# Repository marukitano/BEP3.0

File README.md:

# BEP3.0

**BEP3.0** is an electronics interface for classic BMW K-series motorcycles.

It was developed to make replacing the original instrument cluster ("Brotbox")
with an aftermarket speedometer easier while keeping the original wiring loom
as intact and reversible as possible.

This repository contains the **production and manufacturing files** for the
BEP3.0.

> **License notice:** The files in this repository may be copied, modified and
> used to build a BEP3.0 for **private, non-commercial purposes**.
> **Commercial use is prohibited.**
>
> The commercial right to sell BEP3.0 units is reserved exclusively to
> **Marcus Knop**. Third-party commercial manufacturing or sales require his
> explicit written permission.

## Supported motorcycles

The BEP3.0 was designed for the classic BMW K-series, including:

- BMW K75
- BMW K100
- BMW K1
- BMW K1100

Compatibility with a particular aftermarket instrument depends on the signals
and inputs supported by that instrument.

## What is in this repository?

The repository contains the files used to produce the BEP3.0 hardware, including
PCB/manufacturing data and related production files.

The files are published so that the project can be studied, preserved, repaired
and rebuilt by private users.

## License

### Allowed

- ✅ View and study the files
- ✅ Copy the files for private, non-commercial use
- ✅ Modify the files for private, non-commercial use
- ✅ Build your own BEP3.0 for private, non-commercial use
- ✅ Have a board manufactured for your own private, non-commercial use
- ✅ Share the files non-commercially if the license and attribution remain

### Not allowed

- ❌ Sell BEP3.0 units
- ❌ Sell bare PCBs based on the BEP3.0 design
- ❌ Sell kits based on the BEP3.0 design
- ❌ Offer paid manufacturing or assembly based on these files
- ❌ Use the BEP3.0 design, or substantial parts of it, in another commercial product
- ❌ Use the files for crowdfunding, pre-orders or other commercial fundraising

**All commercial rights remain reserved by Marcus Knop.**

Only Marcus Knop may offer BEP3.0 products for commercial sale. Commercial
manufacturing by third parties is only permitted with his explicit written
permission.

See [LICENSE](LICENSE) for the complete license terms.

> Because commercial use is restricted, this project is **source-available for
> private/non-commercial use** rather than open source in the OSI/open-hardware
> sense.

## Project page

More information about the BEP3.0:

https://maru-labs.com/portfolio/bep3-0-5/

## Contributions and issues

If you discover an error in the production files or documentation, please open
an issue before manufacturing a board.

## Disclaimer

The files are provided **as-is**, without warranty.

If you manufacture hardware from these files, you are responsible for checking
the design, component choices, manufacturing data, electrical safety and
suitability for your intended use.

---

**BEP3.0 / Maru Labs**  
Copyright © Marcus Knop

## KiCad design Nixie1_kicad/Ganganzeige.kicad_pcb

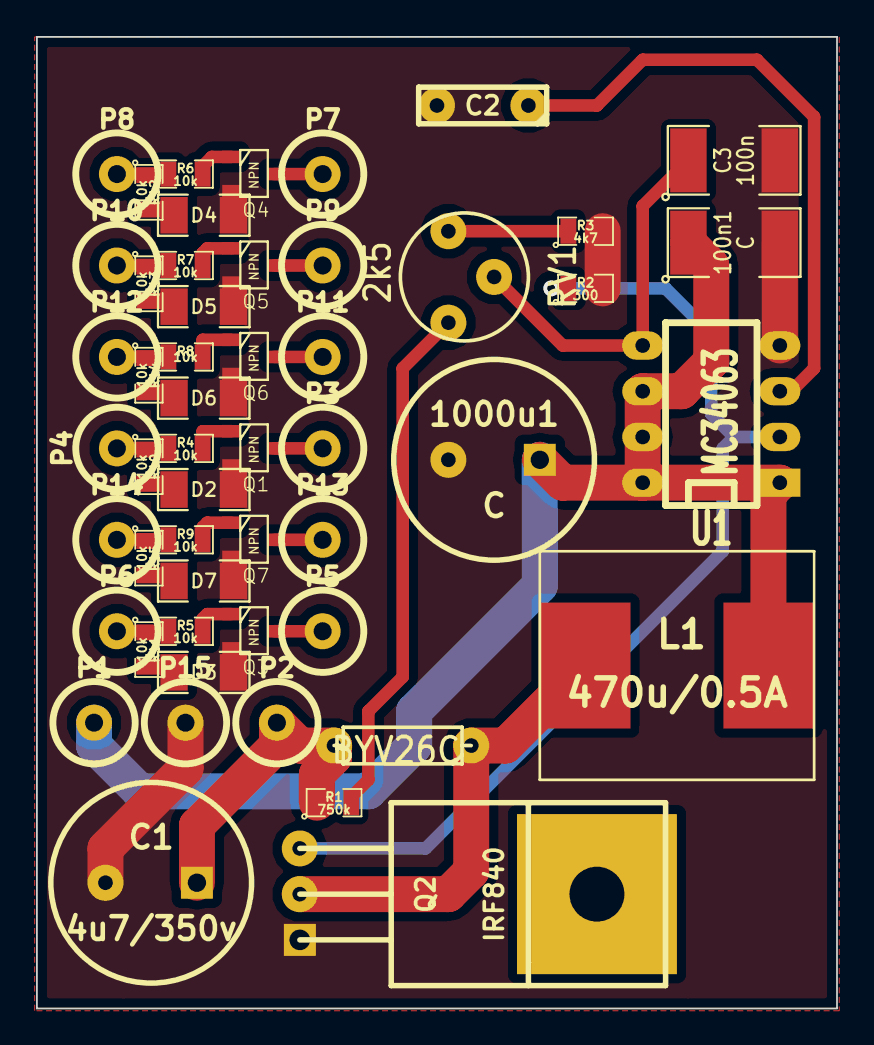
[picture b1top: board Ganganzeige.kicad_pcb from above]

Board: 2 copper layers, 44.4 x 54.0 mm, 52 parts (0 on the bottom side), 33 nets.

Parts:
100n1: C; SM1812L
1000u1: C; C2V10
C1: 4u7/350v; C2V10
C2: 1n; C2
C3: 100n; SM1812L
D1: BYV26C; R3
D2, D3, D4, D5, D6, D7: BYV26C; SM1206
L1: 470u/0.5A; BUZZER
P1, P2, P3, P4, P5, P6, P7, P8, P9, P10, P11, P12, P13, P14, P15: CONN_1; 1pin
Q1, Q3, Q4, Q5, Q6, Q7: NPN; SOT23_INV
Q2: IRF840; TO220
R1: 750k; SM0805
R2: 300; SM0805
R3: 4k7; SM0805
R4, R5, R6, R7, R8, R9, R10, R11, R12, R13, R14, R15: 10k; SM0805
RV1: 2k5; RV2
U1: MC34063; DIP-8__300_ELL

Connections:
GND: 100n1.2, 1000u1.2, C1.2, C2.2, C3.2, D2.2, D3.2, D4.2, D5.2, D6.2, D7.2, P15.1, Q1.1, Q2.1, Q3.1, Q4.1, Q5.1, Q6.1, Q7.1, R2.2, R3.2, U1.4
unnamed: R1.2, RV1.3
unnamed: D1.1, L1.1, Q2.3
unnamed: Q2.2, R2.1, U1.2
unnamed: R3.1, RV1.1
unnamed: C2.1, U1.3
unnamed: C3.1, RV1.2, U1.5
unnamed: D6.1, R14.2
unnamed: D4.1, R12.2
unnamed: P10.1, R7.1, R13.1
unnamed: D5.1, R13.2
unnamed: P12.1, R8.1, R14.1
unnamed: P14.1, R9.1, R15.1
unnamed: D7.1, R15.2
unnamed: D2.1, R10.2
unnamed: D3.1, R11.2
unnamed: P8.1, R6.1, R12.1
unnamed: Q1.2, R4.2
unnamed: P6.1, R5.1, R11.1
unnamed: Q3.2, R5.2
unnamed: Q4.2, R6.2
unnamed: Q5.2, R7.2
unnamed: Q6.2, R8.2
unnamed: Q7.2, R9.2
unnamed: P13.1, Q7.3
unnamed: P4.1, R4.1, R10.1
unnamed: P3.1, Q1.3
unnamed: P5.1, Q3.3
unnamed: P7.1, Q4.3
unnamed: P9.1, Q5.3
unnamed: P11.1, Q6.3
unnamed: 100n1.1, 1000u1.1, L1.2, P1.1, U1.1, U1.6, U1.7, U1.8
unnamed: C1.1, D1.2, P2.1, R1.1
